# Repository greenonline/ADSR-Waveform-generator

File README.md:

# ADSR-Waveform-generator
ADSR Waveform generator, see http://www.yusynth.net/archives/ElectronicDesign/O-Gabor-ADSR-1980.pdf

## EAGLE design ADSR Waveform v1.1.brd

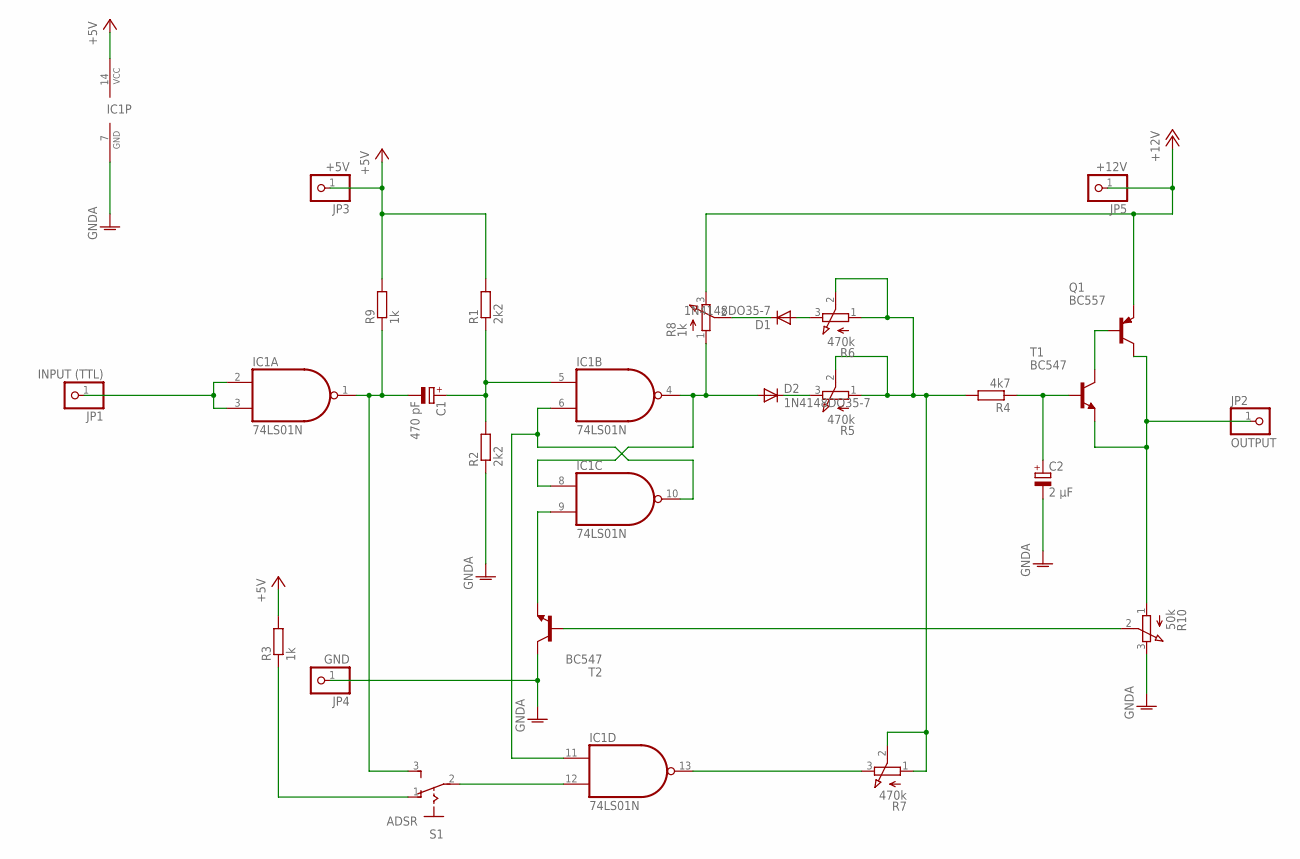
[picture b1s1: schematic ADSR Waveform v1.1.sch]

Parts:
C1: 470 pF; E5-5
C2: 2 µF; E5-5
D1, D2: 1N4148DO35-7; DO35-7
IC1: 74LS01N; DIL14
JP1: INPUT (TTL); 1X01
JP2: OUTPUT; 1X01
JP3: +5V; 1X01
JP4: GND; 1X01
JP5: +12V; 1X01
Q1: BC557; TO92
R1, R2: 2k2; 0204/5
R3, R9: 1k; 0204/5
R4: 4k7; 0204/5
R5, R6, R7: 470k; 3RP/1610N
R8: 1k; 3RP/1610N
R10: 50k; 3RP/1610N
S1: ADSR; 255SB
T1, T2: BC547; TO92

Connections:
+5V: IC1.14 (VCC), JP3.1, R1.2, R3.2, R9.2
+12V: JP5.1, Q1.1 (E), R8.3 (E)
GNDA: C2.-, IC1.7 (GND), JP4.1, R2.1, R10.3 (E), T2.3 (C)
unnamed: IC1.2 (I0), IC1.3 (I1), JP1.1
unnamed: C1.-, IC1.1 (O), R9.1, S1.3 (S)
unnamed: C1.+, IC1.5 (I0), R1.1, R2.2
unnamed: C2.+, R4.1, T1.2 (B)
unnamed: Q1.2 (B), T1.3 (C)
unnamed: R4.2, R5.1 (A), R5.2 (S), R6.1 (A), R6.2 (S), R7.1 (A), R7.2 (S)
unnamed: D2.C, R5.3 (E)
unnamed: D1.A, R6.3 (E)
unnamed: R3.1, S1.1 (O)
unnamed: IC1.12 (I1), S1.2
unnamed: IC1.13 (O), R7.3 (E)
unnamed: R10.2 (S), T2.2 (B)
unnamed: JP2.1, Q1.3 (C), R10.1 (A), T1.1 (E)
unnamed: D2.A, IC1.4 (O), IC1.8 (I0), R8.1 (A)
unnamed: IC1.6 (I1), IC1.10 (O), IC1.11 (I0)
unnamed: IC1.9 (I1), T2.1 (E)
unnamed: D1.C, R8.2 (S)

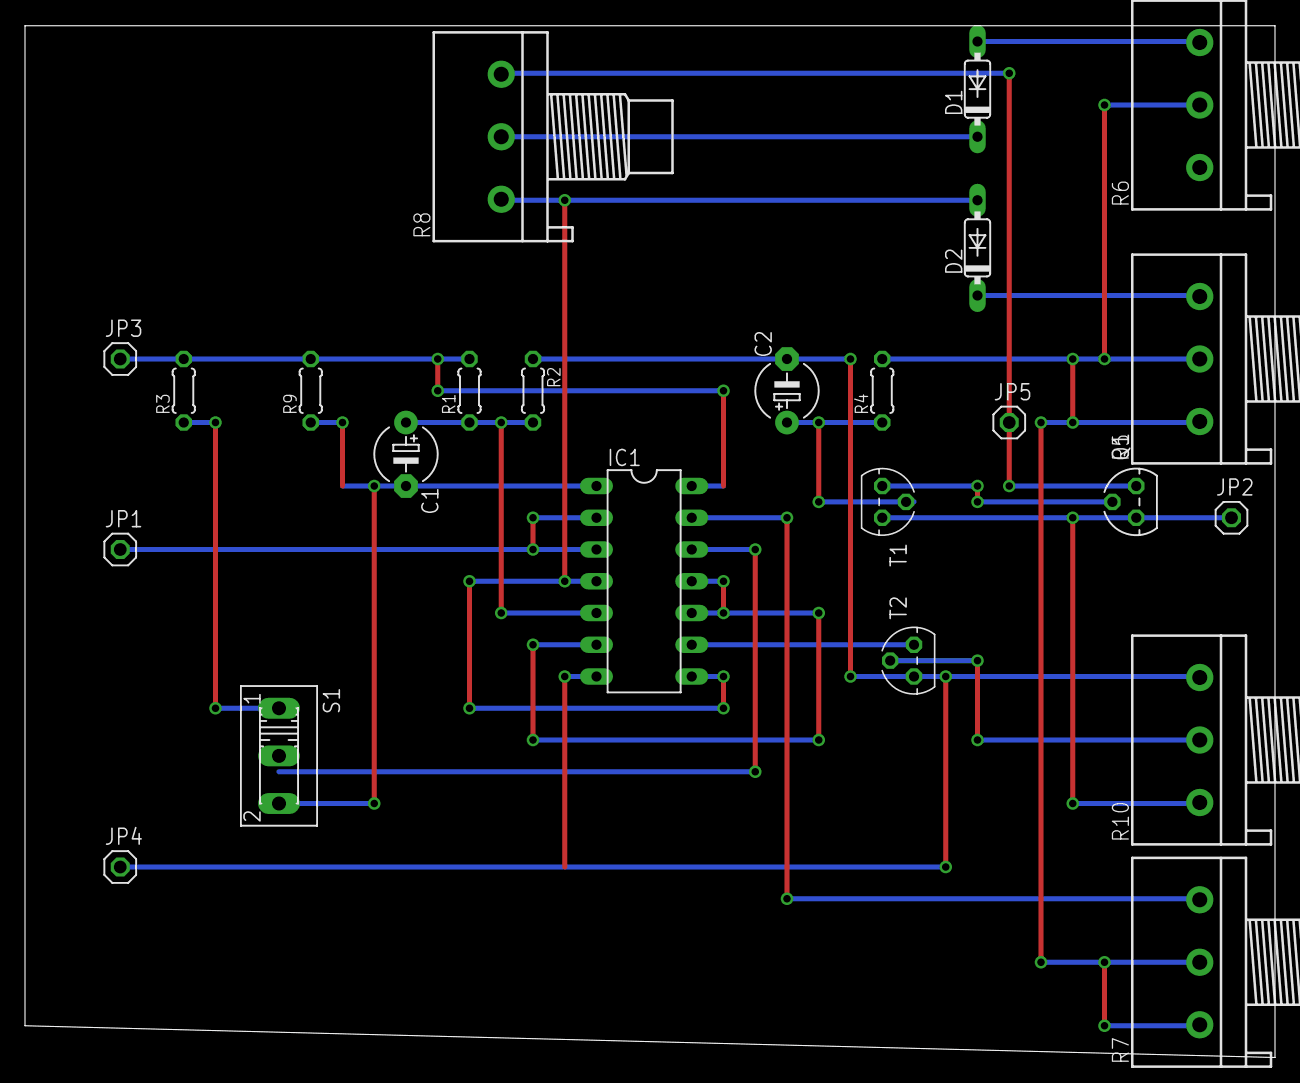
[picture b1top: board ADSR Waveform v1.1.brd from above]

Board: 2 copper layers, 100.0 x 82.5 mm, 24 parts (0 on the bottom side), 20 nets.

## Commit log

2018-06-06 Update README.md
    Fixed link to ADSR
